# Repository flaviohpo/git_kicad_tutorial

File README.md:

# git_kicad_tutorial
Proposta de como utilizar git para versionar projetos de PCB.

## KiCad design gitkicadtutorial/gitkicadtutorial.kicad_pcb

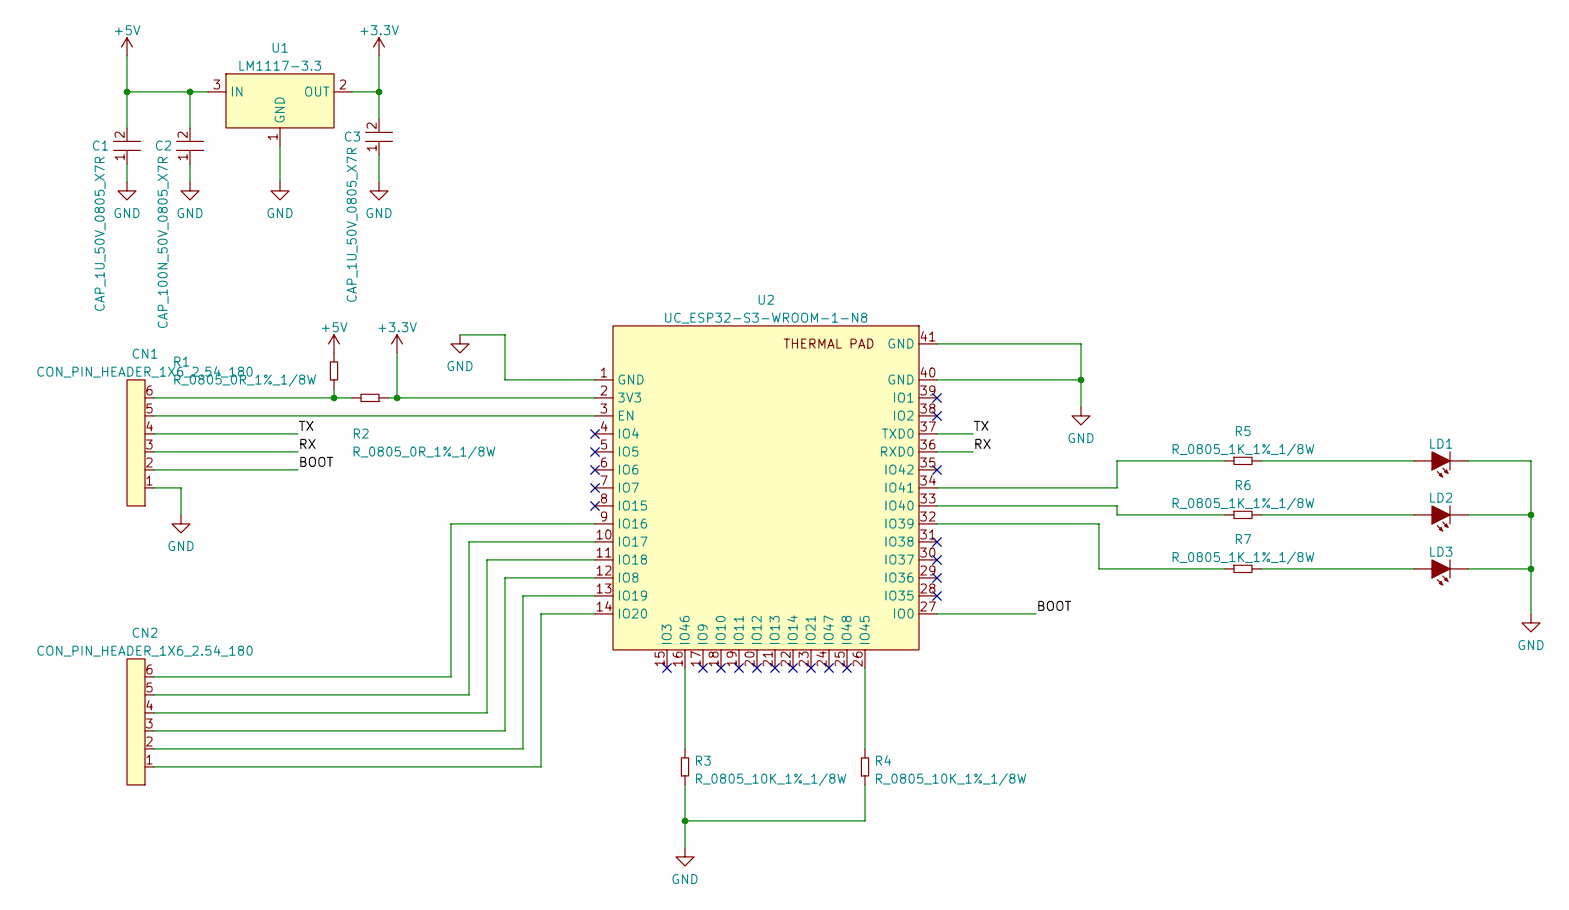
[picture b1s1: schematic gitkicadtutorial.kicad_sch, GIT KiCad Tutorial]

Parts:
C1, C3: CAP_1U_50V_0805_X7R; CAP_0805
C2: CAP_100N_50V_0805_X7R; CAP_0805
CN1, CN2: CON_PIN_HEADER_1X6_2.54_180; pin_header_male_6_2.54_pth
LD1, LD2, LD3: LED_VERDE_0805_L171L-GC-TR; LED_0805
R1, R2: R_0805_0R_1%_1/8W; RES_0805
R3, R4: R_0805_10K_1%_1/8W; RES_0805
R5, R6, R7: R_0805_1K_1%_1/8W; RES_0805
U1: LM1117-3.3; SOT230
U2: UC_ESP32-S3-WROOM-1-N8; ESP32-S3-WROOM-1

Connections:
+3V3: C3.2, R2.1 (CATHODE), U1.2 (OUT), U2.2 (3V3)
+5V: C1.2, C2.2, R1.2 (ANODE), U1.3 (IN)
/BOOT: CN1.2, U2.27 (IO0)
/RX: CN1.3, U2.36 (RXD0)
/TX: CN1.4, U2.37 (TXD0)
GND: C1.1, C2.1, C3.1, CN1.1, LD1.1 (CATHODE), LD2.1 (CATHODE), LD3.1 (CATHODE), R3.1 (CATHODE), R4.1 (CATHODE), U1.1 (GND), U2.1 (GND), U2.40 (GND), U2.41 (GND)
unnamed: LD1.2 (ANODE), R5.2 (ANODE)
unnamed: LD2.2 (ANODE), R6.2 (ANODE)
unnamed: LD3.2 (ANODE), R7.2 (ANODE)
unnamed: CN1.6, R1.1 (CATHODE), R2.2 (ANODE)
unnamed: R3.2 (ANODE), U2.16 (IO46)
unnamed: R4.2 (ANODE), U2.26 (IO45)
unnamed: R5.1 (CATHODE), U2.34 (IO41)
unnamed: R6.1 (CATHODE), U2.33 (IO40)
unnamed: R7.1 (CATHODE), U2.32 (IO39)
unnamed: CN1.5, U2.3 (EN)
unnamed: CN2.6, U2.9 (IO16)
unnamed: CN2.5, U2.10 (IO17)
unnamed: CN2.4, U2.11 (IO18)
unnamed: CN2.3, U2.12 (IO8)
unnamed: CN2.2, U2.13 (IO19)
unnamed: CN2.1, U2.14 (IO20)

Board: 2 copper layers, 17 parts (0 on the bottom side), 22 nets, no tracks yet.

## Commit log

2022-03-17 esquematico criado, nao revisado
2022-03-21 esquematico finalizado
2022-03-21 esquematico revisado
